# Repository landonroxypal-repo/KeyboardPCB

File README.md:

<div align="center">

# KeyboardPCB

*⚠️Under Construction⚠️*

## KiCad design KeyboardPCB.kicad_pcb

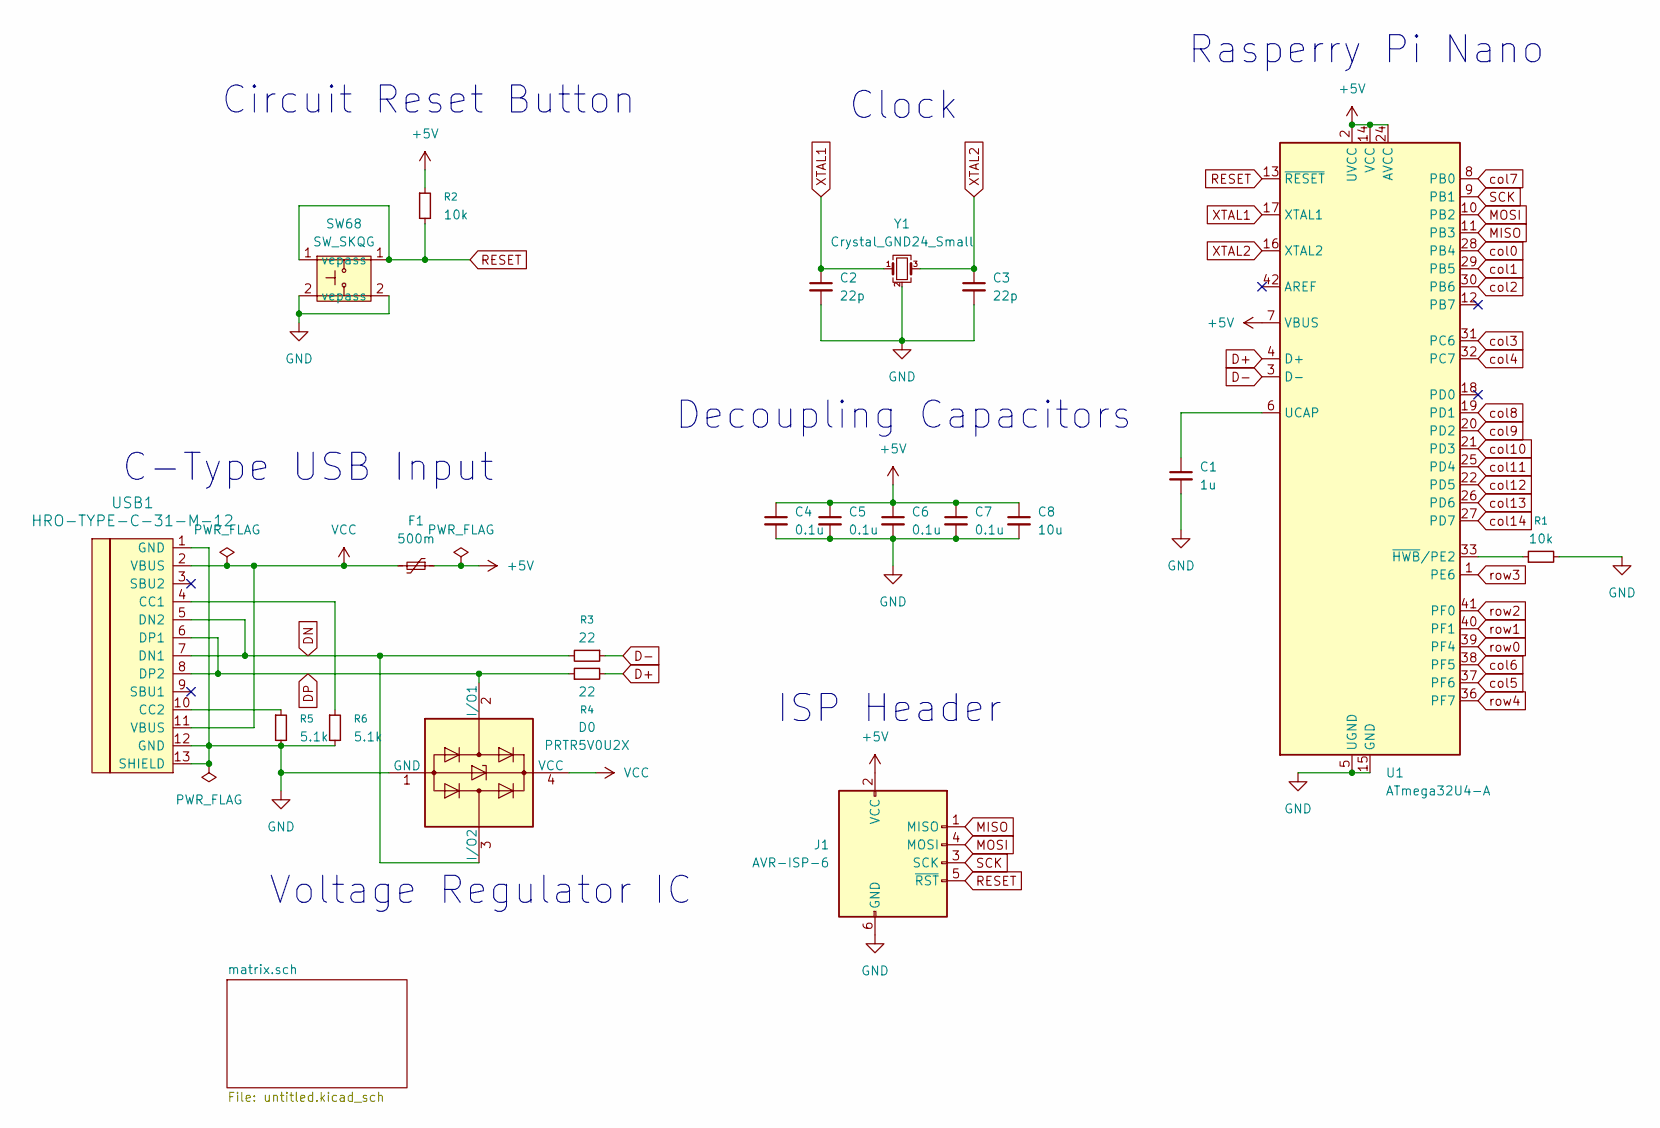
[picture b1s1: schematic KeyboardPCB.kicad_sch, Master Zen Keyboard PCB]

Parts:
C1: 1u; C_0805_2012Metric
C2, C3: 22p; C_0805_2012Metric
C4, C5, C6, C7: 0.1u; C_0805_2012Metric
C8: 10u; C_0805_2012Metric
D0: PRTR5V0U2X; SOT143B
F1: 500m; Fuse_1206_3216Metric_Pad1.42x1.75mm_HandSolder
J1: AVR-ISP-6; Reset_Pretty-Mask
R1, R2: 10k; R_0805_2012Metric_Pad1.20x1.40mm_HandSolder
R3, R4: 22; R_0805_2012Metric_Pad1.20x1.40mm_HandSolder
R5, R6: 5.1k; R_0805_2012Metric_Pad1.20x1.40mm_HandSolder
SW68: SW_SKQG; SW_SPST_SKQG_WithStem
U1: ATmega32U4-A; TQFP-44_10x10mm_P0.8mm
USB1: HRO-TYPE-C-31-M-12; HRO-TYPE-C-31-M-12-HandSoldering
Y1: Crystal_GND24_Small; Crystal_SMD_3225-4Pin_3.2x2.5mm

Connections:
+5V: C4.1, C5.1, C6.1, C7.1, C8.1, F1.1, J1.2 (VCC), R2.1, U1.2 (UVCC), U1.7 (VBUS), U1.14 (VCC), U1.24 (AVCC), U1.34 (VCC), U1.44 (AVCC)
D+: R4.2, U1.4 (D+)
D-: R3.1, U1.3 (D-)
DN: D0.3 (I/O2), R3.2, USB1.5 (DN2), USB1.7 (DN1)
DP: D0.2 (I/O1), R4.1, USB1.6 (DP1), USB1.8 (DP2)
GND: C1.2, C2.2, C3.2, C4.2, C5.2, C6.2, C7.2, C8.2, D0.1 (GND), J1.6 (GND), R1.2, R5.2, R6.2, SW68.2 (pass), U1.5 (UGND), U1.15 (GND), U1.23 (GND), U1.35 (GND), U1.43 (GND), USB1.1 (GND), USB1.12 (GND), USB1.13 (SHIELD), Y1.2 (G), Y1.4 (G)
MISO: J1.1 (MISO), U1.11 (PB3)
MOSI: J1.4 (MOSI), U1.10 (PB2)
unnamed: C1.1, U1.6 (UCAP)
unnamed: R1.1, U1.33 (~HWB/PE2)
unnamed: R6.1, USB1.4 (CC1)
unnamed: R5.1, USB1.10 (CC2)
RESET: J1.5 (~RST), R2.2, SW68.1 (ve), U1.13 (~RESET)
SCK: J1.3 (SCK), U1.9 (PB1)
VCC: D0.4 (VCC), F1.2, USB1.2 (VBUS), USB1.11 (VBUS)
XTAL1: C2.1, U1.17 (XTAL1), Y1.1
XTAL2: C3.1, U1.16 (XTAL2), Y1.3
col0: U1.28 (PB4); also elsewhere on the board
col1: U1.29 (PB5); also elsewhere on the board
col2: U1.30 (PB6); also elsewhere on the board
col3: U1.31 (PC6); also elsewhere on the board
col4: U1.32 (PC7); also elsewhere on the board
col5: U1.37 (PF6); also elsewhere on the board
col6: U1.38 (PF5); also elsewhere on the board
col7: U1.8 (PB0); also elsewhere on the board
col8: U1.19 (PD1); also elsewhere on the board
col9: U1.20 (PD2); also elsewhere on the board
col10: U1.21 (PD3); also elsewhere on the board
col11: U1.25 (PD4); also elsewhere on the board
col12: U1.22 (PD5); also elsewhere on the board
col13: U1.26 (PD6); also elsewhere on the board
col14: U1.27 (PD7); also elsewhere on the board
row0: U1.39 (PF4); also elsewhere on the board
row1: U1.40 (PF1); also elsewhere on the board
row2: U1.41 (PF0); also elsewhere on the board
row3: U1.1 (PE6); also elsewhere on the board
row4: U1.36 (PF7); also elsewhere on the board

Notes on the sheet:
Decoupling Capacitors
C-Type USB Input
Rasperry Pi Nano
Clock
ISP Header
Voltage Regulator IC
Circuit Reset Button

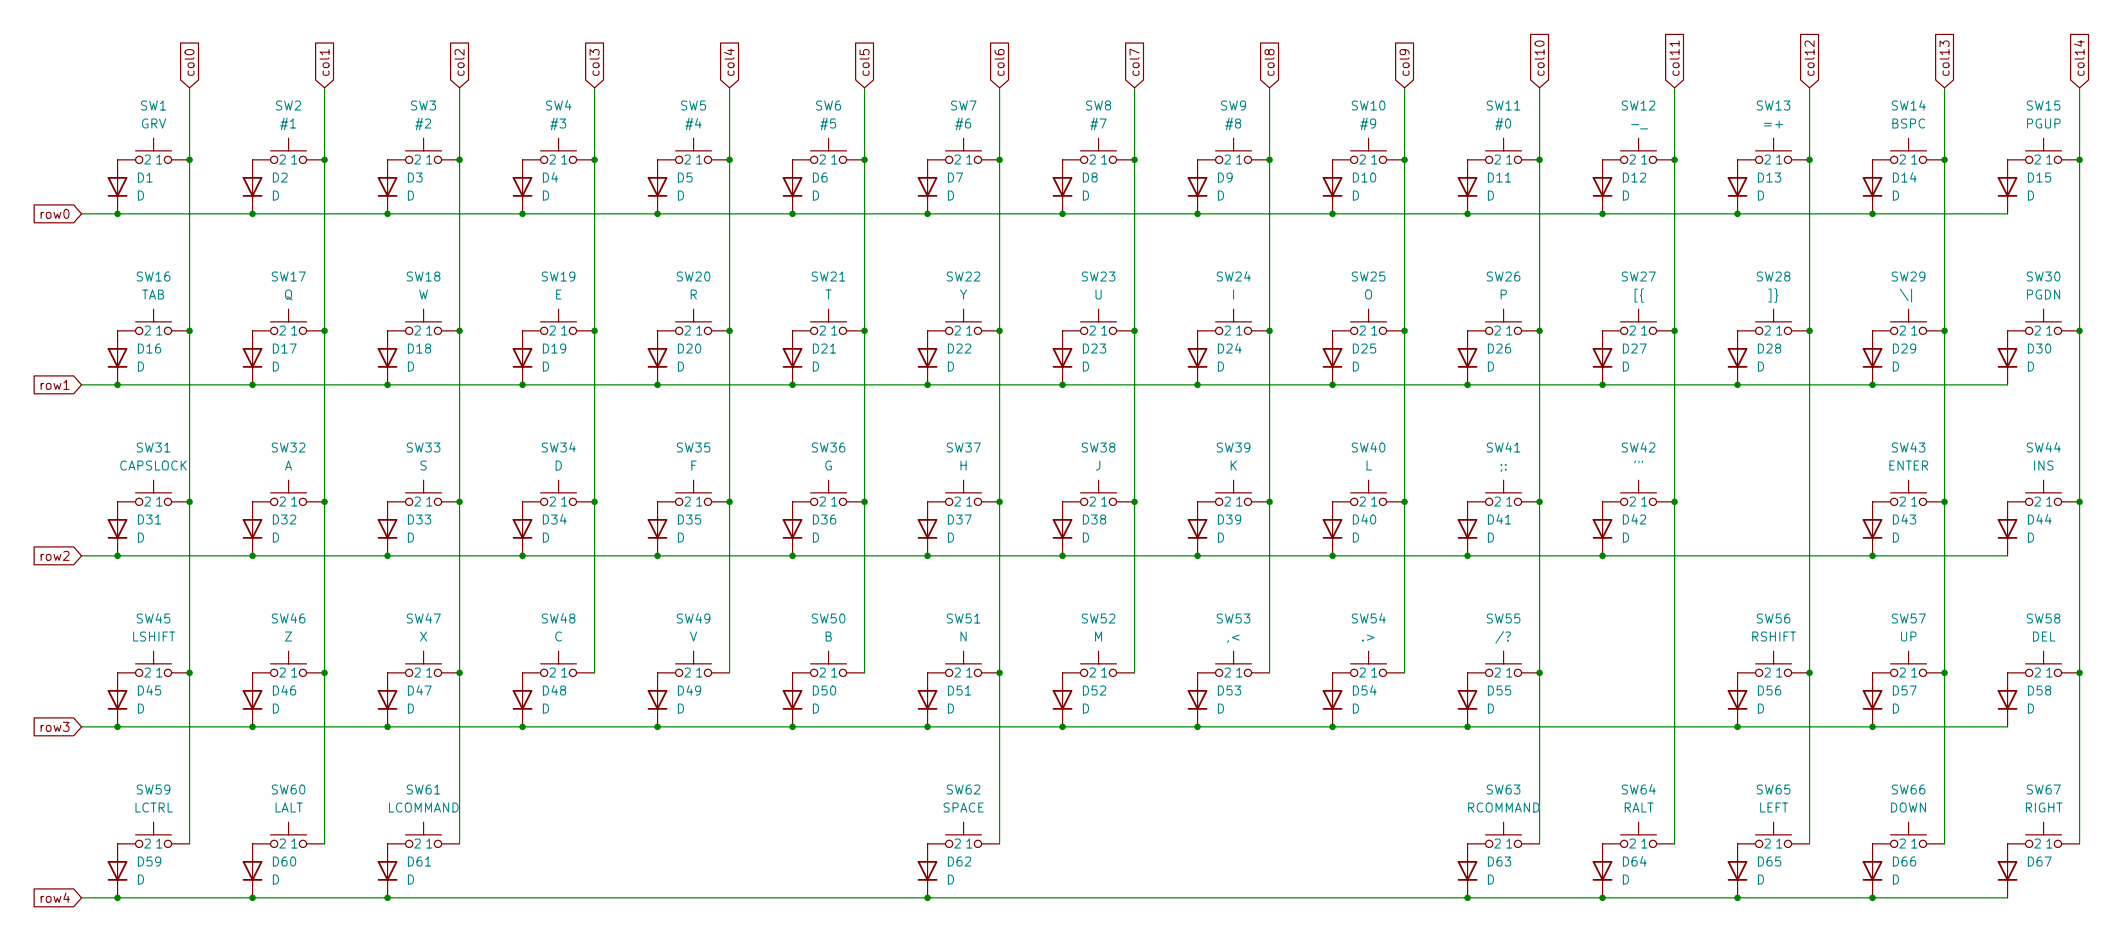
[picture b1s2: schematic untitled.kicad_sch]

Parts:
D1, D2, D3, D4, D5, D6, D7, D8, D9, D10, D11, D12, D13, D14, D15, D16, D17, D18, D19, D20, D21, D22, D23, D24, D25, D26, D27, D28, D29, D30, D31, D32, D33, D34, D35, D36, D37, D38, D39, D40, D41, D42, D43, D44, D45, D46, D47, D48, D49, D50, D51, D52, D53, D54, D55, D56, D57, D58, D59, D60, D61, D62, D63, D64, D65, D66, D67: D; D_SOD-123
SW1: GRV; ALPS-1U
SW2: #1; ALPS-1U
SW3: #2; ALPS-1U
SW4: #3; ALPS-1U
SW5: #4; ALPS-1U
SW6: #5; ALPS-1U
SW7: #6; ALPS-1U
SW8: #7; ALPS-1U
SW9: #8; ALPS-1U
SW10: #9; ALPS-1U
SW11: #0; ALPS-1U
SW12: -_; ALPS-1U
SW13: =+; ALPS-1U
SW14: BSPC; ALPS-2U
SW15: PGUP; ALPS-1U
SW16: TAB; ALPS-1.5U
SW17: Q; ALPS-1U
SW18: W; ALPS-1U
SW19: E; ALPS-1U
SW20: R; ALPS-1U
SW21: T; ALPS-1U
SW22: Y; ALPS-1U
SW23: U; ALPS-1U
SW24: I; ALPS-1U
SW25: O; ALPS-1U
SW26: P; ALPS-1U
SW27: [{; ALPS-1U
SW28: ]}; ALPS-1U
SW29: \|; ALPS-1.5U
SW30: PGDN; ALPS-1U
SW31: CAPSLOCK; ALPS-1.75U
SW32: A; ALPS-1U
SW33: S; ALPS-1U
SW34: D; ALPS-1U
SW35: F; ALPS-1U
SW36: G; ALPS-1U
SW37: H; ALPS-1U
SW38: J; ALPS-1U
SW39: K; ALPS-1U
SW40: L; ALPS-1U
SW41: ;:; ALPS-1U
SW42: '"; ALPS-1U
SW43: ENTER; ALPS-2.25U
SW44: INS; ALPS-1U
SW45: LSHIFT; ALPS-2.25U
SW46: Z; ALPS-1U
SW47: X; ALPS-1U
SW48: C; ALPS-1U
SW49: V; ALPS-1U
SW50: B; ALPS-1U
SW51: N; ALPS-1U
SW52: M; ALPS-1U
SW53: ,<; ALPS-1U
SW54: .>; ALPS-1U
SW55: /?; ALPS-1U
SW56: RSHIFT; ALPS-1.75U
SW57: UP; ALPS-1U
SW58: DEL; ALPS-1U
SW59: LCTRL; ALPS-1.5U
SW60: LALT; ALPS-1.25U
SW61: LCOMMAND; ALPS-1.5U
SW62: SPACE; ALPS-6.5U
SW63: RCOMMAND; ALPS-1U
SW64: RALT; ALPS-1.25U
SW65: LEFT; ALPS-1U
SW66: DOWN; ALPS-1U
SW67: RIGHT; ALPS-1U

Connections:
unnamed: D1.2 (A), SW1.2
unnamed: D2.2 (A), SW2.2
unnamed: D3.2 (A), SW3.2
unnamed: D4.2 (A), SW4.2
unnamed: D5.2 (A), SW5.2
unnamed: D6.2 (A), SW6.2
unnamed: D7.2 (A), SW7.2
unnamed: D8.2 (A), SW8.2
unnamed: D9.2 (A), SW9.2
unnamed: D10.2 (A), SW10.2
unnamed: D11.2 (A), SW11.2
unnamed: D12.2 (A), SW12.2
unnamed: D13.2 (A), SW13.2
unnamed: D14.2 (A), SW14.2
unnamed: D15.2 (A), SW15.2
unnamed: D16.2 (A), SW16.2
unnamed: D17.2 (A), SW17.2
unnamed: D18.2 (A), SW18.2
unnamed: D19.2 (A), SW19.2
unnamed: D20.2 (A), SW20.2
unnamed: D21.2 (A), SW21.2
unnamed: D22.2 (A), SW22.2
unnamed: D23.2 (A), SW23.2
unnamed: D24.2 (A), SW24.2
unnamed: D25.2 (A), SW25.2
unnamed: D26.2 (A), SW26.2
unnamed: D27.2 (A), SW27.2
unnamed: D28.2 (A), SW28.2
unnamed: D29.2 (A), SW29.2
unnamed: D30.2 (A), SW30.2
unnamed: D31.2 (A), SW31.2
unnamed: D32.2 (A), SW32.2
unnamed: D33.2 (A), SW33.2
unnamed: D34.2 (A), SW34.2
unnamed: D35.2 (A), SW35.2
unnamed: D36.2 (A), SW36.2
unnamed: D37.2 (A), SW37.2
unnamed: D38.2 (A), SW38.2
unnamed: D39.2 (A), SW39.2
unnamed: D40.2 (A), SW40.2
unnamed: D41.2 (A), SW41.2
unnamed: D42.2 (A), SW42.2
unnamed: D43.2 (A), SW43.2
unnamed: D44.2 (A), SW44.2
unnamed: D45.2 (A), SW45.2
unnamed: D46.2 (A), SW46.2
unnamed: D47.2 (A), SW47.2
unnamed: D48.2 (A), SW48.2
unnamed: D49.2 (A), SW49.2
unnamed: D50.2 (A), SW50.2
unnamed: D51.2 (A), SW51.2
unnamed: D52.2 (A), SW52.2
unnamed: D53.2 (A), SW53.2
unnamed: D54.2 (A), SW54.2
unnamed: D55.2 (A), SW55.2
unnamed: D56.2 (A), SW56.2
unnamed: D57.2 (A), SW57.2
unnamed: D58.2 (A), SW58.2
unnamed: D59.2 (A), SW59.2
unnamed: D60.2 (A), SW60.2
unnamed: D61.2 (A), SW61.2
unnamed: D62.2 (A), SW62.2
unnamed: D63.2 (A), SW63.2
unnamed: D64.2 (A), SW64.2
unnamed: D65.2 (A), SW65.2
unnamed: D66.2 (A), SW66.2
unnamed: D67.2 (A), SW67.2
col0: SW1.1, SW16.1, SW31.1, SW45.1, SW59.1; also elsewhere on the board
col1: SW2.1, SW17.1, SW32.1, SW46.1, SW60.1; also elsewhere on the board
col2: SW3.1, SW18.1, SW33.1, SW47.1, SW61.1; also elsewhere on the board
col3: SW4.1, SW19.1, SW34.1, SW48.1; also elsewhere on the board
col4: SW5.1, SW20.1, SW35.1, SW49.1; also elsewhere on the board
col5: SW6.1, SW21.1, SW36.1, SW50.1; also elsewhere on the board
col6: SW7.1, SW22.1, SW37.1, SW51.1, SW62.1; also elsewhere on the board
col7: SW8.1, SW23.1, SW38.1, SW52.1; also elsewhere on the board
col8: SW9.1, SW24.1, SW39.1, SW53.1; also elsewhere on the board
col9: SW10.1, SW25.1, SW40.1, SW54.1; also elsewhere on the board
col10: SW11.1, SW26.1, SW41.1, SW55.1, SW63.1; also elsewhere on the board
col11: SW12.1, SW27.1, SW42.1, SW64.1; also elsewhere on the board
col12: SW13.1, SW28.1, SW56.1, SW65.1; also elsewhere on the board
col13: SW14.1, SW29.1, SW43.1, SW57.1, SW66.1; also elsewhere on the board
col14: SW15.1, SW30.1, SW44.1, SW58.1, SW67.1; also elsewhere on the board
row0: D1.1 (K), D2.1 (K), D3.1 (K), D4.1 (K), D5.1 (K), D6.1 (K), D7.1 (K), D8.1 (K), D9.1 (K), D10.1 (K), D11.1 (K), D12.1 (K), D13.1 (K), D14.1 (K), D15.1 (K); also elsewhere on the board
row1: D16.1 (K), D17.1 (K), D18.1 (K), D19.1 (K), D20.1 (K), D21.1 (K), D22.1 (K), D23.1 (K), D24.1 (K), D25.1 (K), D26.1 (K), D27.1 (K), D28.1 (K), D29.1 (K), D30.1 (K); also elsewhere on the board
row2: D31.1 (K), D32.1 (K), D33.1 (K), D34.1 (K), D35.1 (K), D36.1 (K), D37.1 (K), D38.1 (K), D39.1 (K), D40.1 (K), D41.1 (K), D42.1 (K), D43.1 (K), D44.1 (K); also elsewhere on the board
row3: D45.1 (K), D46.1 (K), D47.1 (K), D48.1 (K), D49.1 (K), D50.1 (K), D51.1 (K), D52.1 (K), D53.1 (K), D54.1 (K), D55.1 (K), D56.1 (K), D57.1 (K), D58.1 (K); also elsewhere on the board
row4: D59.1 (K), D60.1 (K), D61.1 (K), D62.1 (K), D63.1 (K), D64.1 (K), D65.1 (K), D66.1 (K), D67.1 (K); also elsewhere on the board

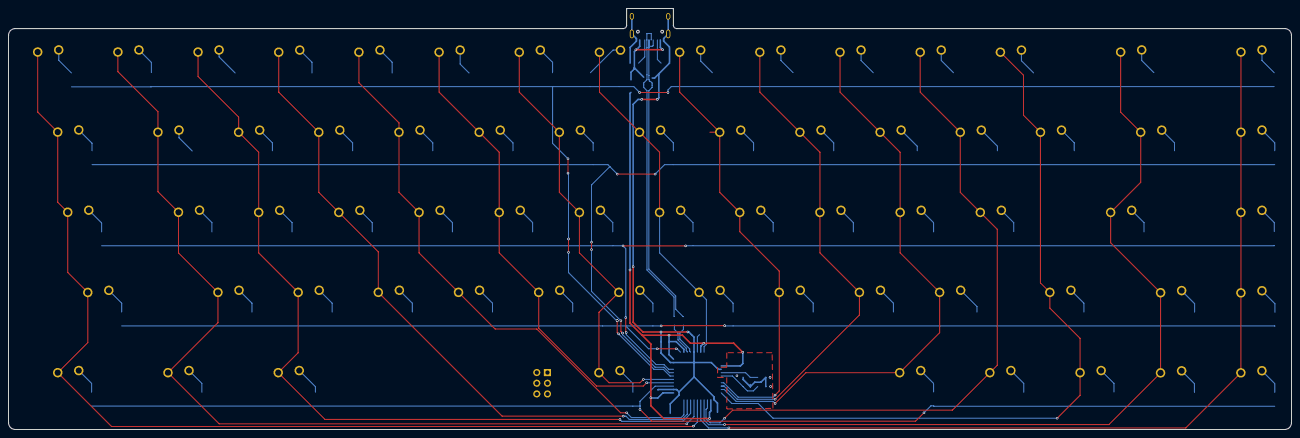
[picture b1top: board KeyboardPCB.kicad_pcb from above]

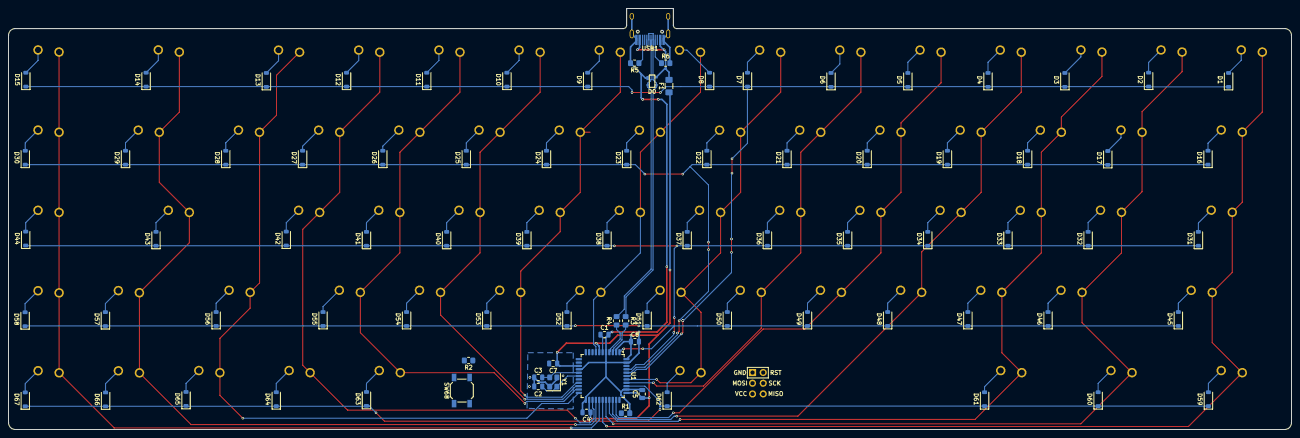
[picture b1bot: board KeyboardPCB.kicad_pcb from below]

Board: 2 copper layers, 304.8 x 100.0 mm, 154 parts (87 on the bottom side), 104 nets.

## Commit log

2026-04-19 Major progress
    - Schematic Finished
    - Footprints applied
    - Working on PCB now
2026-04-19 PCB File Visualized.
2026-04-20 Moved local library
2026-04-20 Fixed local library not having schematic
2026-04-20 Backup files.
2026-04-20 Keyboard keys positioned
2026-04-27 Layout progress.
    Moved the diodes to each of their keys.
    Mostly finished placing capacitors, resistors, and other components.
2026-04-27 Locks
2026-04-28 PCB Layout finished.
    Placed all components on the board.
    Figured out where all the decoupling capacitors go!
    Also fixed an issue with one of the decoupling capacitors not being 10 uF.
2026-04-28 Lock
2026-04-28 Fixed C-Type USB.
    Fixed the C-Type USB not having a model on the 3D model of the PCB.
2026-04-30 Attempted netting
2026-05-02 Fixed routes being way too large
2026-05-02 Lock file
2026-05-04 Routed about half of the PCB
2026-05-08 Routed around MCU
2026-05-08 Extra save
2026-05-12 Continued routing
2026-05-13 Finished Keyboard Matrix routing
2026-06-17 Under Construction README
